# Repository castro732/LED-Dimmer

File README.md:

# LED Dimmer

## Description

LED Dimmer for use in LED strips (at 12V) using a 555 and a power transistor IRF530.

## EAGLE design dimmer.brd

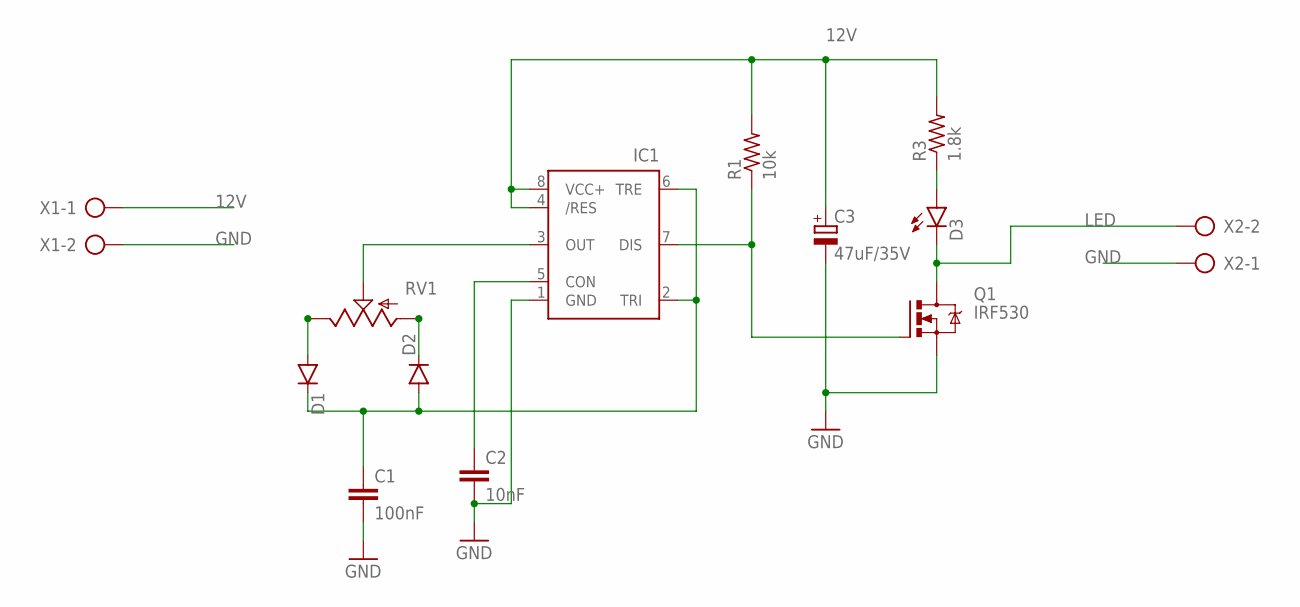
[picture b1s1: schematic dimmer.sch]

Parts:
C1: 100nF; C050-025X075
C2: 10nF; C050-025X075
C3: 47uF/35V; E2,5-7
D1, D2: DIODE1N4148; DIODE-1N4148
D3: LED5MM
IC1: NE555P; DIL-08
Q1: IRF530; TO220BV
R1: 10k; 0207/10
R3: 1.8k; 0207/10
RV1: POT-RV16AF-20; POT_ALPHA_RV16AF-20
X1, X2: AK300/2

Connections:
12V: C3.+, IC1.4 (/RES), IC1.8 (VCC+), R1.2, R3.2, X1.1
GND: C1.2, C2.2, C3.-, IC1.1 (GND), Q1.S, X1.2, X2.1
LED: D3.K (C), Q1.D, X2.2
unnamed: D1.A, RV1.3 (E)
unnamed: D2.C, RV1.1 (A)
unnamed: IC1.7 (DIS), Q1.G, R1.1
unnamed: D3.A, R3.1
unnamed: IC1.3 (OUT), RV1.2 (S)
unnamed: C1.1, D1.C, D2.A, IC1.2 (TRI), IC1.6 (TRE)
unnamed: C2.1, IC1.5 (CON)

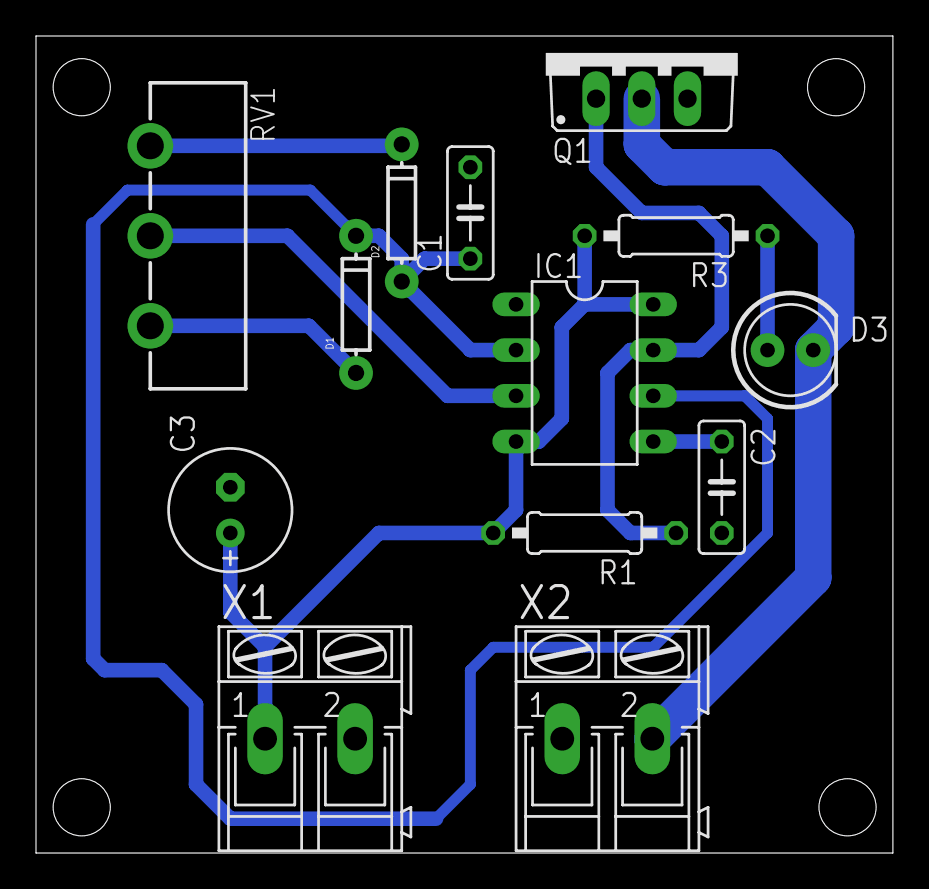
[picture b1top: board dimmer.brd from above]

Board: 2 copper layers, 47.6 x 45.4 mm, 13 parts (0 on the bottom side), 10 nets.

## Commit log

2016-08-06 Add files

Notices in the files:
parts and their libraries:
SparkFun-DiscreteSemi: Licensing: Creative Commons ShareAlike 4.0 International - https://creativecommons.org/licenses/by-sa/4.0
